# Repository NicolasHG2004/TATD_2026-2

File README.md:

# Temas-Avanzados-en-T-cnicas-Digitales-2026-2

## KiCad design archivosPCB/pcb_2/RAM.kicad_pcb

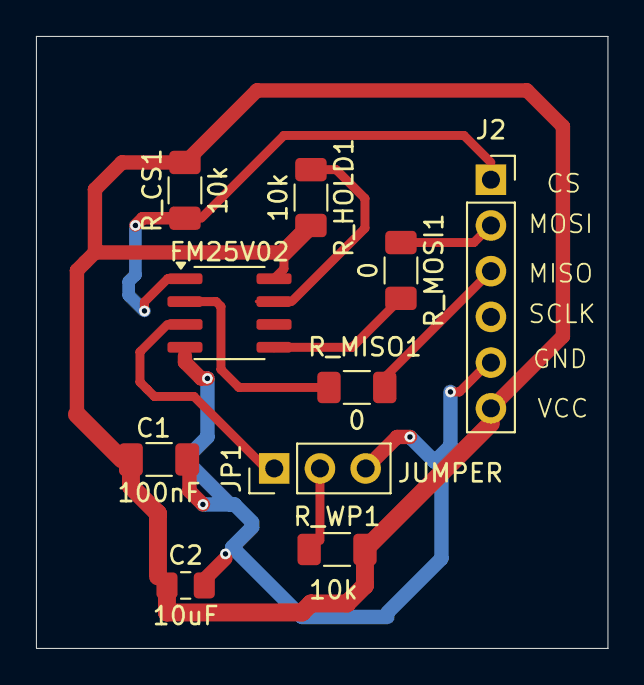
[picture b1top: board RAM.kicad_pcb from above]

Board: 2 copper layers, 31.8 x 34.0 mm, 10 parts (0 on the bottom side), 10 nets.

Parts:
C1: 100nF; C_1206_3216Metric_Pad1.33x1.80mm_HandSolder
C2: 10uF; C_0805_2012Metric_Pad1.18x1.45mm_HandSolder
FM25V02: FM25V02; SOIC-8_3.9x4.9mm_P1.27mm
J2: Conn_01x06; PinSocket_1x06_P2.54mm_Vertical
JP1: JUMPER; PinHeader_1x03_P2.54mm_Vertical
R_CS1: 10k; R_1206_3216Metric_Pad1.30x1.75mm_HandSolder
R_HOLD1: 10k; R_1206_3216Metric_Pad1.30x1.75mm_HandSolder
R_MISO1: 0; R_1206_3216Metric_Pad1.30x1.75mm_HandSolder
R_MOSI1: 0; R_1206_3216Metric_Pad1.30x1.75mm_HandSolder
R_WP1: 10k; R_1206_3216Metric_Pad1.30x1.75mm_HandSolder

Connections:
+3.3V: C1.1, C2.1, FM25V02.8 (VCC), J2.6, R_CS1.2, R_HOLD1.2, R_WP1.2
/Cs: FM25V02.1 (SS/), J2.1, R_CS1.1
/MISO: J2.3, R_MISO1.2
/MOSI: J2.2, R_MOSI1.1
GND: C1.2, C2.2, FM25V02.4 (GND), J2.5, JP1.3 (B)
unnamed: FM25V02.7 (HOLD/), R_HOLD1.1
unnamed: FM25V02.2 (MISO), R_MISO1.1
unnamed: FM25V02.5 (MOSI), R_MOSI1.2
unnamed: FM25V02.3 (WP/), JP1.1 (A)
unnamed: JP1.2 (C), R_WP1.1
